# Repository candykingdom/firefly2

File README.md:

# Firefly2

Wireless LED control for Burning Man art installations, bikes, and wearables. Devices driving WS2812 strips self-organize over 915 MHz RFM69 radios into a flood mesh with exactly one master, share a network clock via heartbeats, and render effects as pure functions of network time — so every device animates in sync without streaming frames.

New to the project? Start with [GETTING_STARTED.md](GETTING_STARTED.md). Working in the code (human or agent)? The mental model lives in [docs/index.md](docs/index.md) and the shared Claude Code/Codex ground rules in [CLAUDE.md](CLAUDE.md).

## Web simulator (test without hardware)

```bash
python3 -m http.server 8642 -d sim
# open http://localhost:8642/
```

A zero-dependency browser simulator of the whole system: every effect and palette on the real device catalog, synced to a scrubbable network clock, with master-mode autoplay and control overrides. Byte-exact against the firmware (enforced by tests: `npm test`). See [docs/simulator.md](docs/simulator.md).

## Building firmware

Firmware builds with [PlatformIO](https://platformio.org/) (`pip install platformio`). One env per device target:

```bash
pio run -e node                  # SAMD21 rfboard node (node-arm64 on Apple silicon)
pio run -e fancy-node            # STM32G030 node
pio run -e controller            # STM32G070 handheld controller
pio run -e dmx                   # ESP32 DMX bridge
pio run -e fancy-node -t upload  # flash via ST-Link
pio device monitor               # 115200 baud
```

Note: `[env:node]`'s bossac `platform_packages` entry is OS-specific — uncomment the right line in [platformio.ini](platformio.ini) for your OS. Full env/pin/flag details: [docs/build-and-test.md](docs/build-and-test.md).

### Programming over USB

The `fancy-node` device can be programmed either using an STLink, or via USB port. To program via USB, you must first install stm32loader using pip (`pip install stm32loader`). You may also need to pass the port (typically `/dev/ttyUSB0`), e.g. `pio run -e fancy-node-usb -t upload --upload-port /dev/ttyUSB0`.

### Saving device description in flash

Both `node` and `fancy-node` support reading the [`DeviceDescription`](lib/device/DeviceDescription.hpp) from flash. The modes are defined by the `DeviceMode` enum within [`DeviceDescription.hpp`](lib/device/DeviceDescription.hpp). They work as follows:

- `CURRENT_FROM_HEADER`: use the `current` device defined in [`Devices.hpp`](lib/device/Devices.hpp)
- `READ_FROM_FLASH`: read the device saved in flash, if present. If not present (determined by the validity of `check_value`), fall back to `current`.
- `WRITE_TO_FLASH`: write `current` to flash, and then use it. This will only write the device to flash if it is different, to avoid causing flash wear.

## Tests & linting

The platform-independent core (`lib/`, `src/generic/`) builds on the host against fakes, with ASan + UBSan on (and fatal). Requires cmake and a GCC/Clang toolchain (on Windows, use WSL or similar):

```bash
mkdir -p build && cd build
cmake .. -DBUILD_SIMULATOR=false   # true builds the SDL desktop simulator too
make && make test
./smalltests --gtest_filter=RadioStateMachineTest*
```

```bash
./lint.sh check     # clang-format, Google style — CI enforces this
./lint.sh format    # format in place
./ci.sh             # exactly what CI runs: cmake + smalltests + largetests
node --test "sim/test/cases/*.test.mjs"   # simulator suite, incl. firmware byte-exactness
npm run test:e2e    # served UI/API/canvas journeys in Chromium and Firefox
```

CI (GitHub Actions): host tests, lint, `node`/`fancy-node`/`controller` firmware
builds, the simulator suite, and CodeQL C/C++ security scanning.

## Repo layout

| Path | Contents |
|---|---|
| `lib/`, `src/generic/` | Platform-independent core: radio protocol, mesh, effects, LED management |
| `src/arduino/` | Hardware backends (FastLED, RadioHead RFM69) |
| `src/devices/` | One `main` per device target (node, fancy-node, controller, dmx) |
| `test/` | Host GoogleTest suites + `FakeNetwork` multi-node mesh simulation |
| `sim/` | Browser simulator (production C++ renderer via committed Wasm, usable without hardware) |
| `docs/` | Architecture and per-subsystem notes — start at [docs/index.md](docs/index.md) |
| `hardware/`, `boards/`, `bootloader/` | PCB designs, PlatformIO board definitions, bootloaders |
| `specs/` | Spec-kit feature specs (spec → plan → tasks workflow, see CLAUDE.md) |

## For agents & contributors

- [CLAUDE.md](CLAUDE.md) — the canonical guidance for Claude Code and Codex, including build commands, architecture, and the **invariants you must not break**. Codex reaches the same file through `AGENTS.md`; shared skills remain canonical under `.claude/skills/` and are exposed to Codex through `.agents/skills/`.
- [docs/](docs/index.md) — per-subsystem research notes (radio/network, LED/effects, devices, build/test, hardware). Update them when you change documented behavior.
- Substantial features go through the spec-kit workflow (`speckit-specify` → `plan` →
  `tasks` → `implement`; use `/` in Claude Code or `$` in Codex); specs live in `specs/`.

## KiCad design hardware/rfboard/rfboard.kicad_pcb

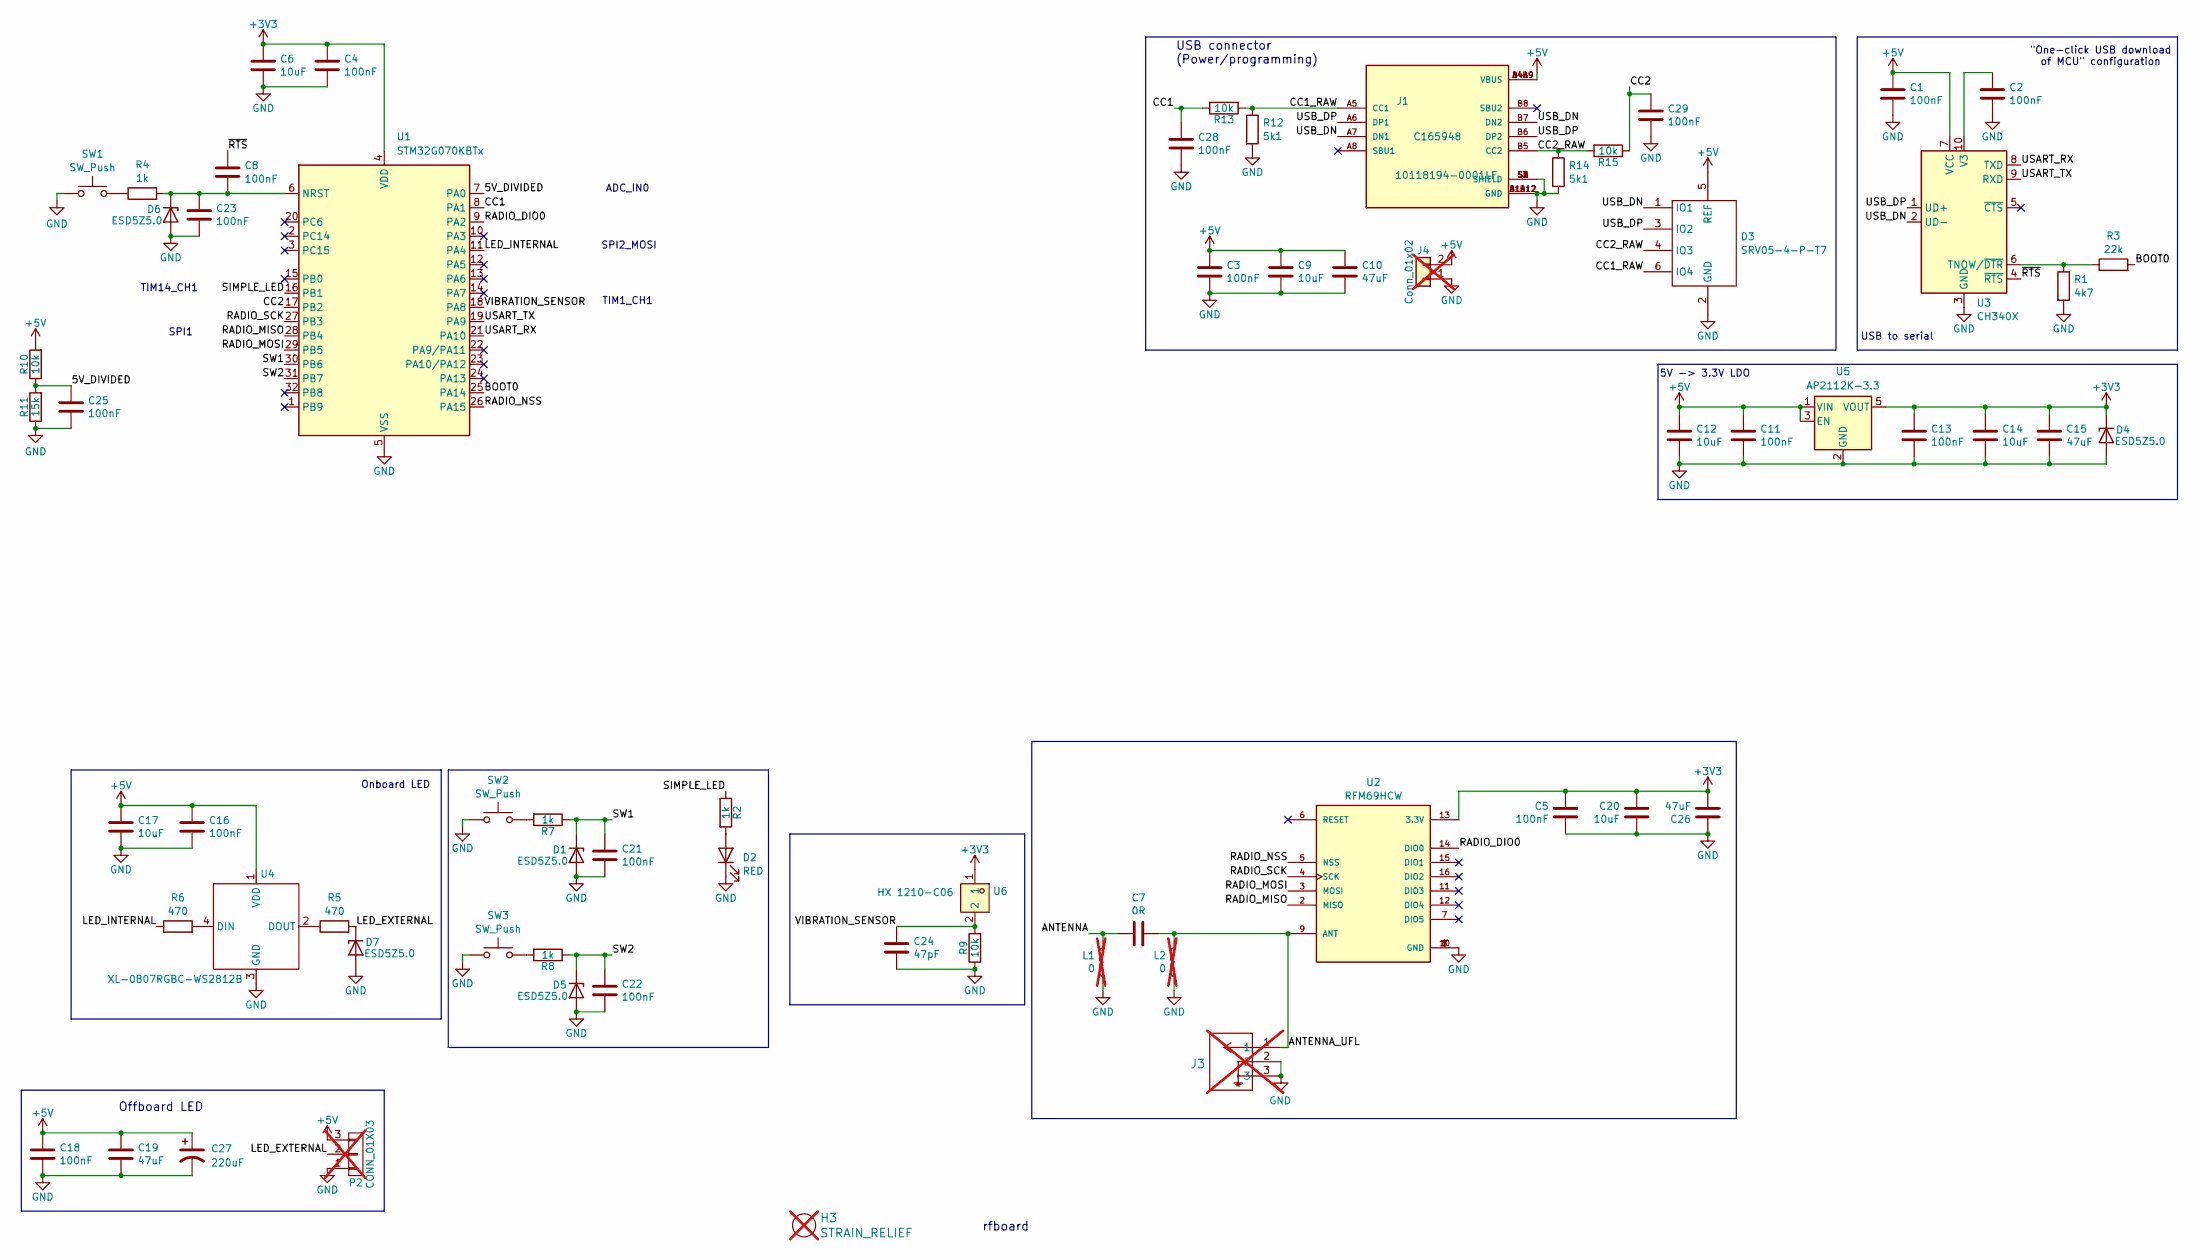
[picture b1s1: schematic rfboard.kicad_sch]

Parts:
C1, C2, C3, C4, C5, C8, C11, C13, C16, C18, C21, C22, C23, C25, C28, C29: 100nF; C_0402_1005Metric; LCSC C307331
C6, C9, C12, C14, C17, C20: 10uF; C_0603_1608Metric; LCSC C96446
C7: 0R; C_0402_1005Metric_Pad0.74x0.62mm_HandSolder; LCSC C17168
C10, C15, C19, C26: 47uF; C_1206_3216Metric; LCSC C426659
C24: 47pF; C_0402_1005Metric; LCSC C1567
C27: 220uF; CP_Elec_6.3x5.8; Voltage 16V; LCSC C25170689
D1, D4, D5, D6, D7: ESD5Z5.0; D_SOD-523; LCSC C5199848
D2: RED; LED_0603_1608Metric; LCSC C2286
D3: SRV05-4-P-T7; SOT-23-6; LCSC C85364
H3: STRAIN_RELIEF; 3_pin_2.54mm_pitch_strain_relief; not fitted
J1: 10118194-0001LF; HRO_TYPE-C-31-M-12; PARTREV A; LCSC C165948
J3: 2337019-1; CONN_2337019-1; MPN 2337019-1; not fitted
J4: Conn_01x02; PinHeader_1x02_P2.54mm_Vertical_NoPlastic; not fitted
L1, L2: 0; L_0402_1005Metric_Pad0.77x0.64mm_HandSolder; not fitted
P2: CONN_01X03; PinHeader_1x03_P2.54mm_Vertical; not fitted
R1: 4k7; R_0402_1005Metric; LCSC C25900
R2, R4, R7, R8: 1k; R_0402_1005Metric; LCSC C11702
R3: 22k; R_0402_1005Metric; LCSC C25768
R5, R6: 470; R_0402_1005Metric; LCSC C25117
R9, R10, R13, R15: 10k; R_0402_1005Metric; LCSC C25744
R11: 15k; R_0402_1005Metric; LCSC C25756
R12, R14: 5k1; R_0402_1005Metric; LCSC C25905
SW1, SW2, SW3: SW_Push; SW_TACTILE_5.1MM_TS-1187A-C-D-B; LCSC C318884
U1: STM32G070KBTx; LQFP-32_7x7mm_P0.8mm; LCSC C529339
U2: RFM69HCW; RFM69HCW-minimalpads
U3: CH340X; MSOP-10_3x3mm_P0.5mm; LCSC C3035748
U4: XL-0807RGBC-WS2812B; LED-SMD_4P-L2.0-W1.8_CY-0807; LCSC C3646929
U5: AP2112K-3.3; SOT-23-5; LCSC C51118
U6: HX 1210-C06; SMD-2P_L2.9-W2.4_C9900033648; LCSC Part C42371120

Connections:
+3V3: C4.1, C5.1, C6.1, C13.1, C14.1, C15.1, C20.1, C26.2, D4.1 (K), U1.4 (VDD), U2.13 (3.3V), U5.5 (VOUT), U6.1
+5V: C1.1, C3.1, C9.1, C10.1, C11.1, C12.1, C16.1, C17.1, C18.1, C19.1, C27.1, D3.5 (REF), J1.A4B9 (VBUS), J1.B4A9 (VBUS), J4.2, P2.3, R10.2, U3.7 (VCC), U4.1 (VDD), U5.1 (VIN), U5.3 (EN)
/5V_DIVIDED: C25.1, R10.1, R11.2, U1.7 (PA0)
/ANTENNA: C7.1, L1.1
/ANTENNA_UFL: C7.2, J3.1, L2.1, U2.9 (ANT)
/BOOT0: R3.2, U1.25 (PA14)
/CC1: C28.1, R13.2, U1.8 (PA1)
/CC1_RAW: D3.6 (IO4), J1.A5 (CC1), R12.1, R13.1
/CC2: C29.1, R15.1, U1.17 (PB2)
/CC2_RAW: D3.4 (IO3), J1.B5 (CC2), R14.1, R15.2
/LED_EXTERNAL: D7.1 (K), P2.2, R5.2
/LED_INTERNAL: R6.1, U1.11 (PA4)
/RADIO_DIO0: U1.9 (PA2), U2.14 (DIO0)
/RADIO_MISO: U1.28 (PB4), U2.2 (MISO)
/RADIO_MOSI: U1.29 (PB5), U2.3 (MOSI)
/RADIO_NSS: U1.26 (PA15), U2.5 (NSS)
/RADIO_SCK: U1.27 (PB3), U2.4 (SCK)
/SIMPLE_LED: R2.1, U1.16 (PB1)
/SW1: C21.1, D1.1 (K), R7.1, U1.30 (PB6)
/SW2: C22.1, D5.1 (K), R8.1, U1.31 (PB7)
/USART_RX: U1.21 (PA10), U3.8 (TXD)
/USART_TX: U1.19 (PA9), U3.9 (RXD)
/USB_DN: D3.1 (IO1), J1.A7 (DN1), J1.B7 (DN2), U3.2 (UD-)
/USB_DP: D3.3 (IO2), J1.A6 (DP1), J1.B6 (DP2), U3.1 (UD+)
/VIBRATION_SENSOR: C24.1, R9.2, U1.18 (PA8), U6.2
/~RTS: C8.1, U3.4 (~RTS)
GND: C1.2, C2.2, C3.2, C4.2, C5.2, C6.2, C9.2, C10.2, C11.2, C12.2, C13.2, C14.2, C15.2, C16.2, C17.2, C18.2, C19.2, C20.2, C21.2, C22.2, C23.2, C24.2, C25.2, C26.1, C27.2, C28.2, C29.2, D1.2 (A), D2.1 (K), D3.2 (GND), D4.2 (A), D5.2 (A), D6.2 (A), D7.2 (A), J1.A1B12 (GND), J1.B1A12 (GND), J1.S1 (SHIELD), J1.S2 (SHIELD), J1.S3 (SHIELD), J1.S4 (SHIELD), J3.2, J3.3, J4.1, L1.2, L2.2, P2.1, R1.2, R9.1, R11.1, R12.2, R14.2, SW1.1, SW2.1, SW3.1, U1.5 (VSS), U2.1 (GND), U2.8 (GND), U2.10 (GND), U3.3 (GND), U4.3 (GND), U5.2 (GND)
unnamed: D2.2 (A), R2.2
unnamed: C8.2, C23.1, D6.1 (K), R4.2, U1.6 (NRST)
unnamed: R4.1, SW1.2
unnamed: R7.2, SW2.2
unnamed: R8.2, SW3.2
unnamed: R1.1, R3.1, U3.6 (TNOW/~DTR)
unnamed: C2.1, U3.10 (V3)
unnamed: R6.2, U4.4 (DIN)
unnamed: R5.1, U4.2 (DOUT)

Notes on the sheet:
5V -> 3.3V LDO
USB connector (Power/programming)
rfboard
TIM14_CH1
Offboard LED
SPI2_MOSI
USB to serial
"One-click USB download of MCU" configuration
SPI1
ADC_IN0
TIM1_CH1
Onboard LED

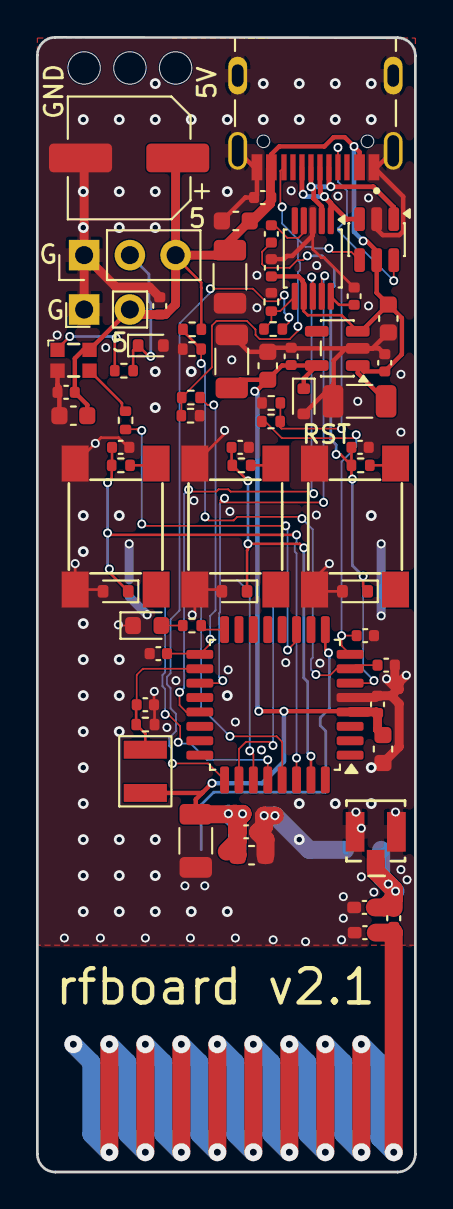
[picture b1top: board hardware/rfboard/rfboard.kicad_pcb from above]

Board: 4 copper layers, 21.0 x 63.0 mm, 67 parts (1 on the bottom side), 36 nets.

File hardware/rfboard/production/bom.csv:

Designator,Footprint,Quantity,Value,LCSC Part #
"C1, C11, C13, C16, C18, C2, C21, C22, C23, C25, C28, C29, C3, C4, C5, C8",0402,16,100nF,C307331
"C10, C15, C19, C26",1206,4,47uF,C96123
"C12, C14, C17, C20, C6, C9",0603,6,10uF,C96446
C24,0402,1,47pF,C1567
C27,CP_Elec_6.3x5.8,1,220uF,C25170689
C7,0402,1,0R,C17168
"D1, D4, D5, D6, D7",D_SOD-523,5,ESD5Z5.0,C5199848
D2,0603,1,RED,C2286
D3,SOT-23-6,1,SRV05-4-P-T7,C85364
J1,HRO_TYPE-C-31-M-12,1,10118194-0001LF,C165948
R1,0402,1,4k7,C25900
"R10, R13, R15, R9",0402,4,10k,C25744
R11,0402,1,15k,C25756
"R12, R14",0402,2,5k1,C25905
"R2, R4, R7, R8",0402,4,1k,C11702
R3,0402,1,22k,C25768
"R5, R6",0402,2,470,C25117
"SW1, SW2, SW3",SW_TACTILE_5.1MM_TS-1187A-C-D-B,3,SW_Push,C318884
U1,LQFP-32_7x7mm_P0.8mm,1,STM32G070KBTx,C529339
U2,RFM69HCW-minimalpads,1,RFM69HCW,
U3,MSOP-10_3x3mm_P0.5mm,1,CH340X,C3035748
U4,LED-SMD_4P-L2.0-W1.8_CY-0807,1,XL-0807RGBC-WS2812B,C3646929
U5,SOT-23-5,1,AP2112K-3.3,C51118
U6,SMD-2P_L2.9-W2.4_C9900033648,1,HX 1210-C06,C42371120

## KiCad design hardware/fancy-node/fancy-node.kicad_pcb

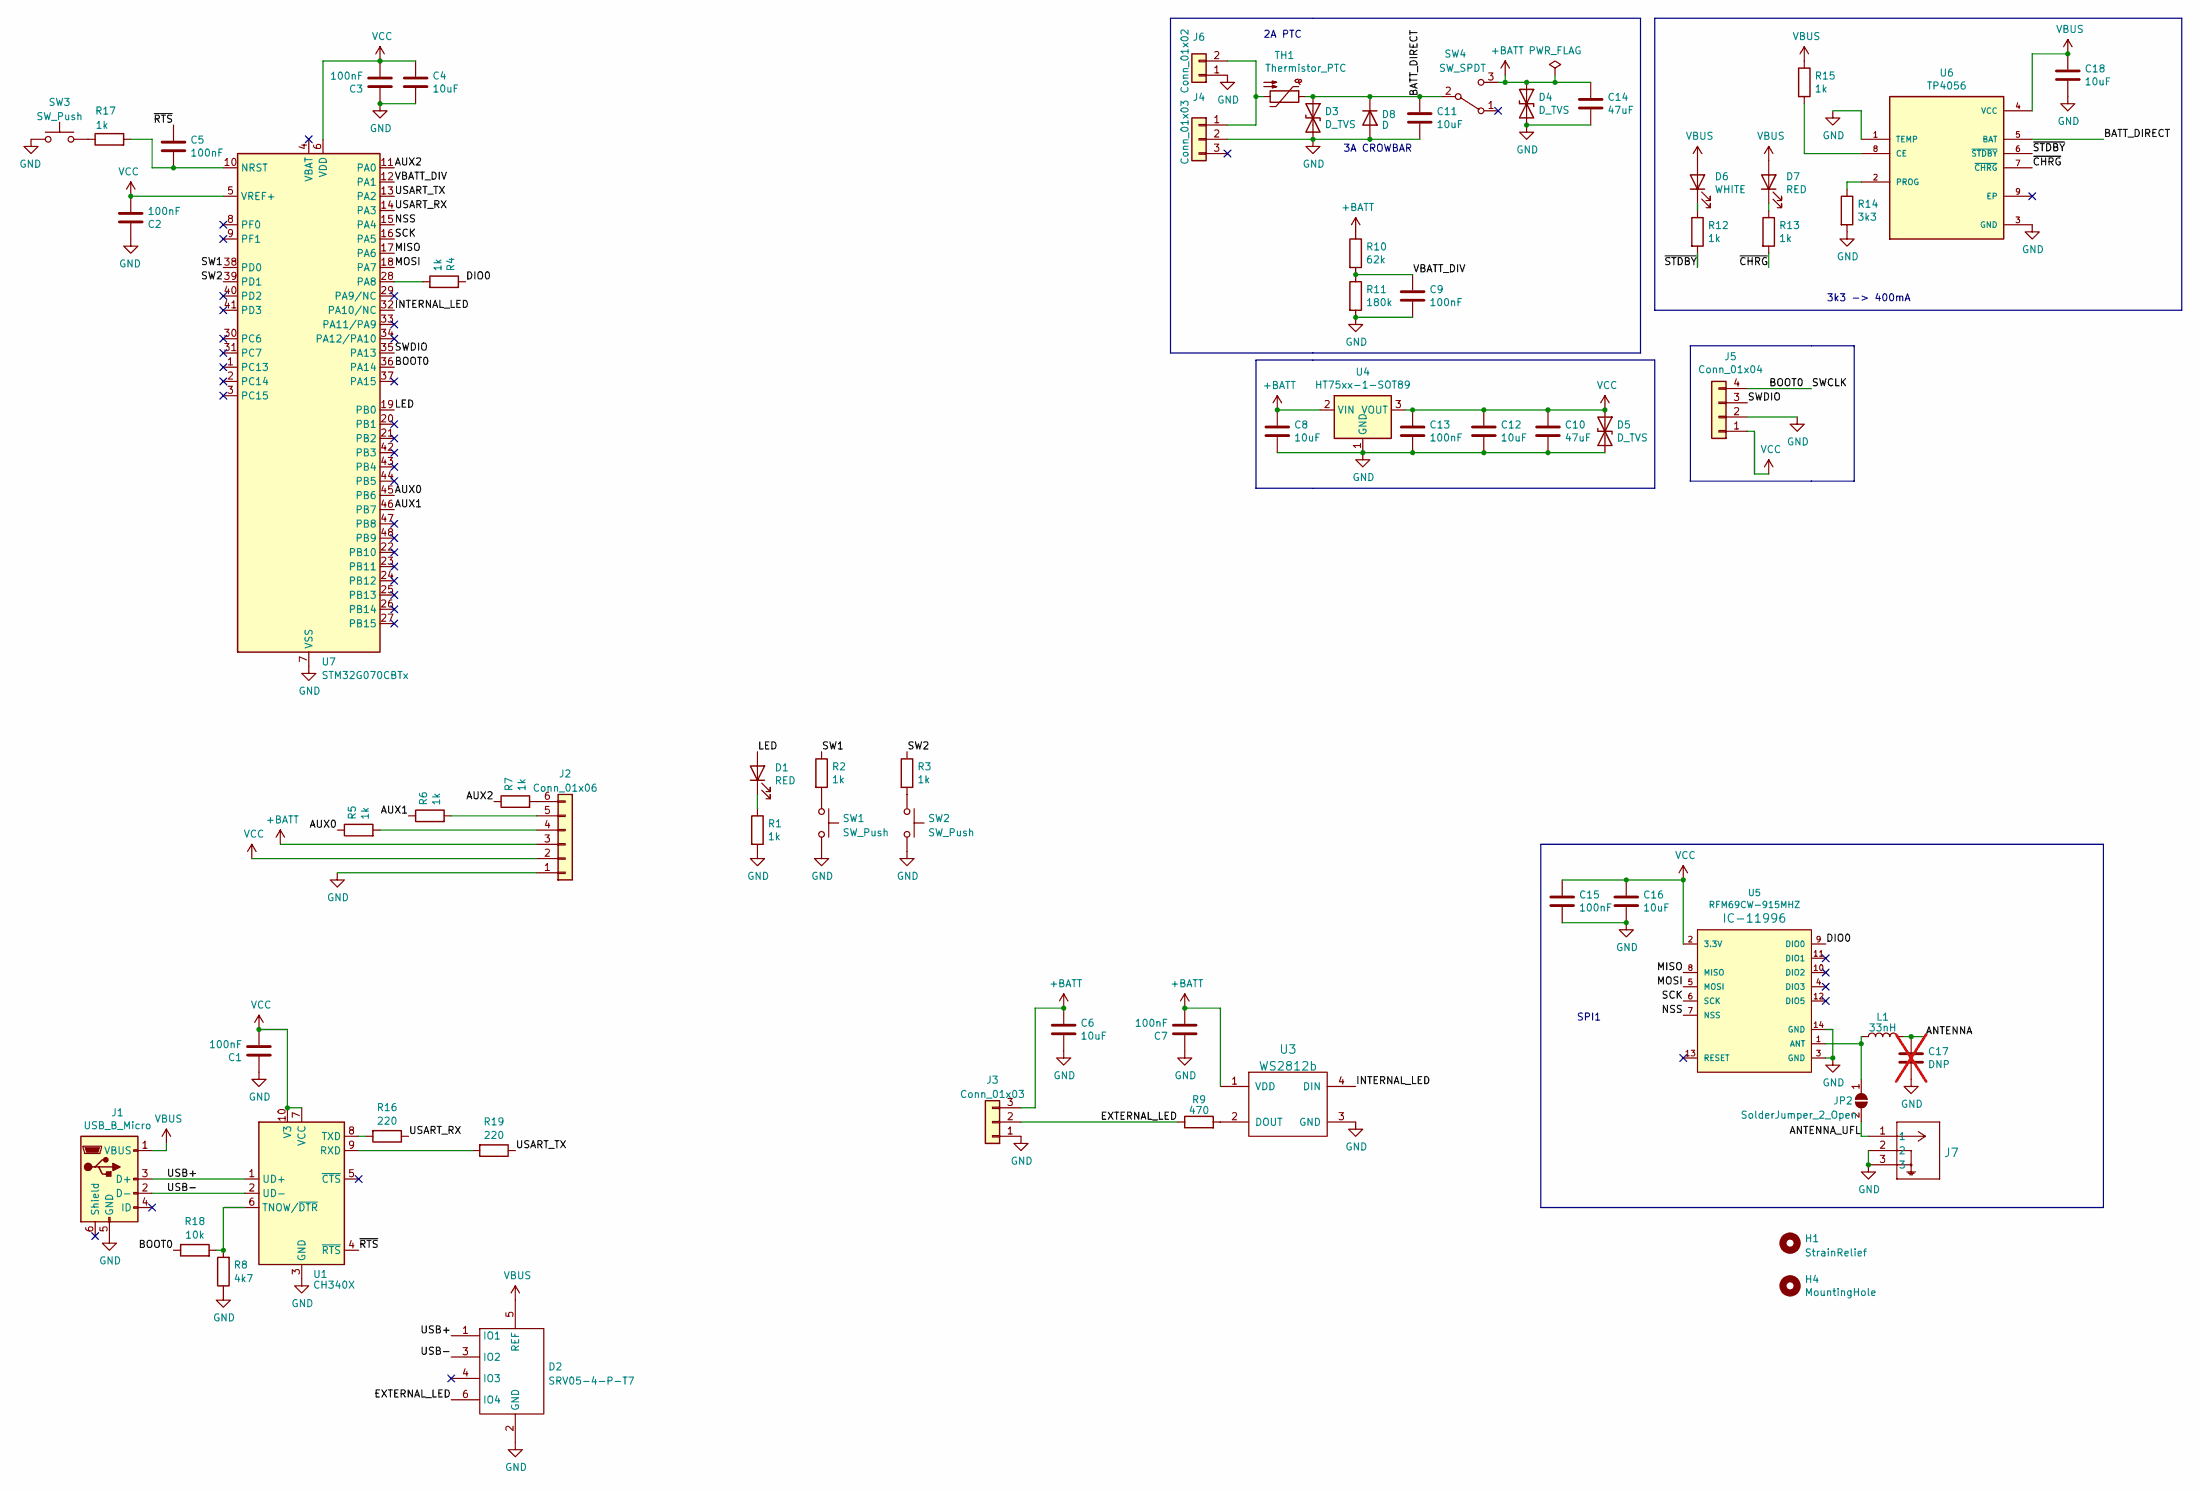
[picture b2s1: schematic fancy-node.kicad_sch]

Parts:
C1, C2, C3, C5, C7, C9, C13, C15: 100nF; C_0402_1005Metric_Pad0.74x0.62mm_HandSolder; LCSC C307331
C4, C6, C8, C11, C12, C16, C18: 10uF; C_0603_1608Metric; LCSC C96446
C10, C14: 47uF; C_1206_3216Metric; LCSC C96123
C17: DNP; C_0402_1005Metric_Pad0.74x0.62mm_HandSolder; not fitted
D1, D7: RED; LED_0603_1608Metric; LCSC C2286
D2: SRV05-4-P-T7; SOT-23-6; LCSC C85364
D3, D4, D5: D_TVS; D_SMB; LCSC C78395
D6: WHITE; LED_0603_1608Metric; LCSC C2290
D8: D; D_SMA; LCSC C8678
H1: StrainRelief; 3_pin_2.54mm_pitch_strain_relief
H4: MountingHole; MountingHole_3.2mm_M3
J1: USB_B_Micro; FRAMATOME_10118194-0001LF_fixed_bridges; LCSC C132563
J2: Conn_01x06; PinHeader_1x06_P2.54mm_Vertical
J3: Conn_01x03; PinHeader_1x03_P2.54mm_Horizontal
J4: Conn_01x03; MiniPV_78208-X03XXX_1x03_P2.54mm_Polarized_Horizontal
J5: Conn_01x04; PinHeader_1x04_P2.54mm_Vertical
J6: Conn_01x02; JST_Micro_1x02_P1.25mm_Horizontal
J7: 2337019-1; CONN_2337019-1; MPN 2337019-1
JP2: SolderJumper_2_Open; SolderJumper-2_P1.3mm_Open_TrianglePad1.0x1.5mm
L1: 33nH; L_0402_1005Metric; LCSC C113114
R1, R2, R3, R4, R5, R6, R7, R12, R13, R15, R17: 1k; R_0402_1005Metric; LCSC C11702
R8: 4k7; R_0402_1005Metric; LCSC C25900
R9: 470; R_0603_1608Metric; LCSC C23179
R10: 62k; R_0603_1608Metric; LCSC C23221
R11: 180k; R_0603_1608Metric; LCSC C22827
R14: 3k3; R_0603_1608Metric; LCSC C22978
R16, R19: 220; R_0402_1005Metric; LCSC C25091
R18: 10k; R_0402_1005Metric; LCSC C25744
SW1, SW2, SW3: SW_Push; SW_TACTILE_3mmx3.5mm_TS-1071SA-A4B3-D4; LCSC C498310
SW4: SW_SPDT; SW_SLIDE_SPDT_K3-1204D-L; LCSC C2909229
TH1: Thermistor_PTC; Fuse_1812_4532Metric_Pad1.30x3.40mm_HandSolder; LCSC C89650
U1: CH340X; MSOP-10_3x3mm_P0.5mm; LCSC C3035748
U3: WS2812b; LED_XINGLIGHT_WS2812B_PLCC4_5.0x5.0mm_P3.2mm; LCSC C2843785
U4: HT75xx-1-SOT89; SOT-89-3; LCSC C14289
U5: RFM69CW-915MHZ; RFM69CW-XXXS2
U6: TP4056; SOP-8_3.9x4.9mm_P1.27mm_Thermal; LCSC C382139
U7: STM32G070CBTx; LQFP-48_7x7mm_P0.5mm; LCSC C529338

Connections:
+BATT: C6.2, C7.2, C8.2, C14.2, D4.1 (A1), J2.3, J3.3, R10.1, SW4.3 (C), U3.1 (VDD), U4.2 (VIN)
/ANTENNA: C17.1, L1.2
/ANTENNA_UFL: J7.1, JP2.2 (B)
/AUX0: R5.1, U7.45 (PB6)
/AUX1: R6.1, U7.46 (PB7)
/AUX2: R7.1, U7.11 (PA0)
/BATT_DIRECT: C11.2, D3.1 (A1), D8.1 (K), SW4.2 (B), TH1.1, U6.5 (BAT)
/BOOT0: J5.4, R18.1, U7.36 (PA14)
/DIO0: R4.1, U5.9 (DIO0)
/EXTERNAL_LED: D2.6 (IO4), J3.2, R9.1
/INTERNAL_LED: U3.4 (DIN), U7.32 (PA10/NC)
/LED: D1.2 (A), U7.19 (PB0)
/MISO: U5.8 (MISO), U7.17 (PA6)
/MOSI: U5.5 (MOSI), U7.18 (PA7)
/NSS: U5.7 (NSS), U7.15 (PA4)
/SCK: U5.6 (SCK), U7.16 (PA5)
/SW1: R2.1, U7.38 (PD0)
/SW2: R3.1, U7.39 (PD1)
/SWDIO: J5.3, U7.35 (PA13)
/USART_RX: R16.1, U7.14 (PA3)
/USART_TX: R19.1, U7.13 (PA2)
/USB+: D2.1 (IO1), J1.3 (D+), U1.1 (UD+)
/USB-: D2.3 (IO2), J1.2 (D-), U1.2 (UD-)
/VBATT_DIV: C9.1, R10.2, R11.1, U7.12 (PA1)
/~CHRG: R13.2, U6.7 (~CHRG)
/~RTS: C5.1, U1.4 (~RTS)
/~STDBY: R12.2, U6.6 (~STDBY)
GND: C1.1, C2.1, C3.1, C4.2, C6.1, C7.1, C8.1, C9.2, C10.1, C11.1, C12.1, C13.2, C14.1, C15.2, C16.1, C17.2, C18.1, D2.2 (GND), D3.2 (A2), D4.2 (A2), D5.2 (A2), D8.2 (A), J1.5 (GND), J2.1, J3.1, J4.2, J5.2, J6.1, J7.2, J7.3, R1.2, R8.1, R11.2, R14.2, SW1.2, SW2.2, SW3.2, U1.3 (GND), U3.3 (GND), U4.1 (GND), U5.3 (GND), U5.14 (GND), U6.1 (TEMP), U6.3 (GND), U7.7 (VSS)
unnamed: D1.1 (K), R1.1
unnamed: D6.1 (K), R12.1
unnamed: D7.1 (K), R13.1
unnamed: J2.4, R5.2
unnamed: J2.5, R6.2
unnamed: J2.6, R7.2
unnamed: J4.1, J6.2, TH1.2
unnamed: JP2.1 (A), L1.1, U5.1 (ANT)
unnamed: R2.2, SW1.1
unnamed: R3.2, SW2.1
unnamed: R17.1, SW3.1
unnamed: R19.2, U1.9 (RXD)
unnamed: R8.2, R18.2, U1.6 (TNOW/~DTR)
unnamed: R16.2, U1.8 (TXD)
unnamed: R9.2, U3.2 (DOUT)
unnamed: R15.2, U6.8 (CE)
unnamed: R14.1, U6.2 (PROG)
unnamed: C5.2, R17.2, U7.10 (NRST)
unnamed: R4.2, U7.28 (PA8)
VBUS: C18.2, D2.5 (REF), D6.2 (A), D7.2 (A), J1.1 (VBUS), R15.1, U6.4 (VCC)
VCC: C1.2, C2.2, C3.2, C4.1, C10.2, C12.2, C13.1, C15.1, C16.2, D5.1 (A1), J2.2, J5.1, U1.7 (VCC), U1.10 (V3), U4.3 (VOUT), U5.2 (3.3V), U7.5 (VREF+), U7.6 (VDD)

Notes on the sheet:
3k3 -> 400mA
3A CROWBAR
SPI1
2A PTC

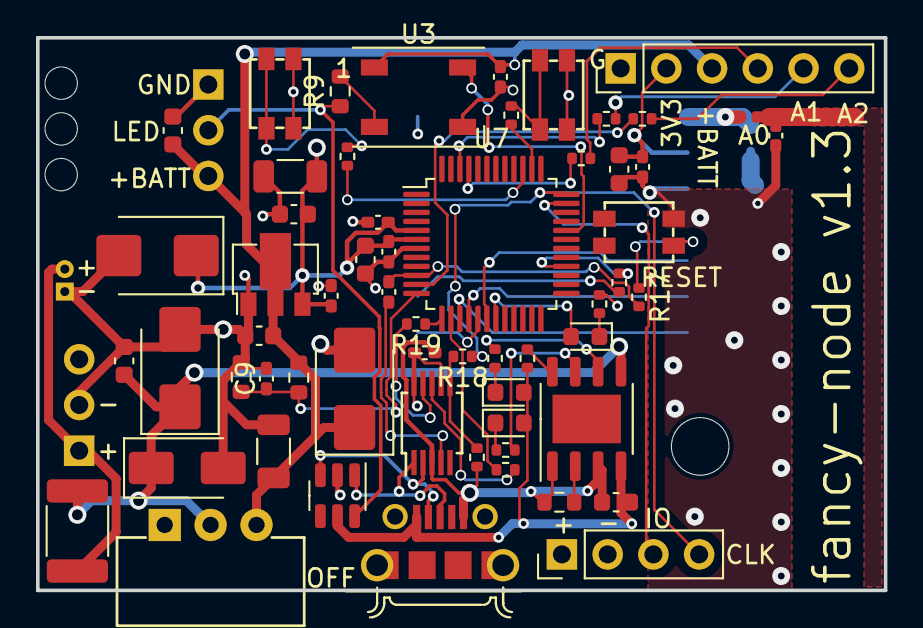
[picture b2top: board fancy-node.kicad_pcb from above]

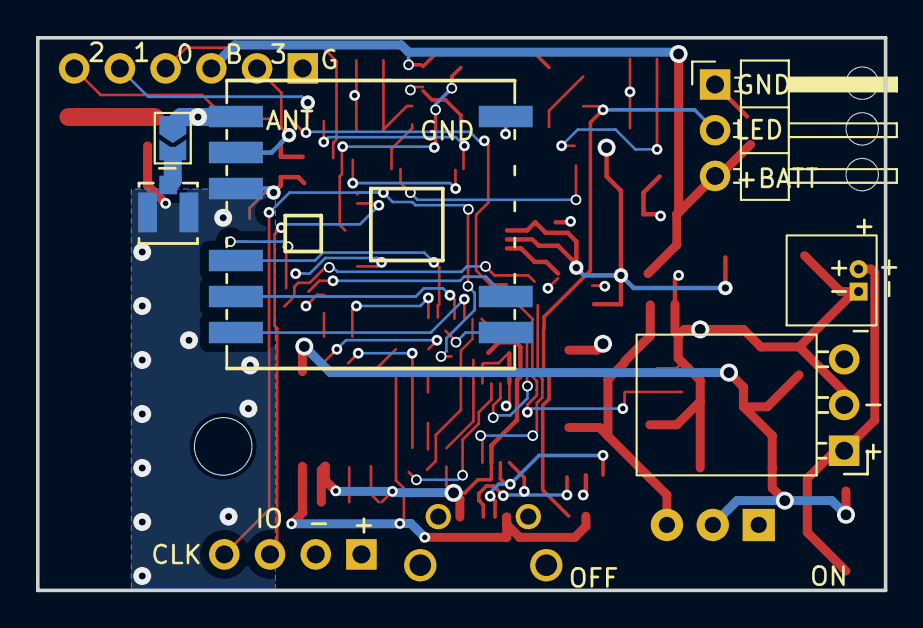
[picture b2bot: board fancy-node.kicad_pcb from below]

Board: 4 copper layers, 47.1 x 30.7 mm, 67 parts (6 on the bottom side), 49 nets.

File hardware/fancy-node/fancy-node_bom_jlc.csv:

"Comment","Designator","Footprint","LCSC Part #"
"100nF","C1,C2,C3,C5,C7,C9,C13,C15","C_0402_1005Metric_Pad0.74x0.62mm_HandSolder","C307331"
"10uF","C4,C6,C8,C11,C12,C16,C18","C_0603_1608Metric","C96446"
"47uF","C10,C14","C_1206_3216Metric","C96123"
"RED","D1,D7","LED_0603_1608Metric","C2286"
"SRV05-4-P-T7","D2","SOT-23-6","C85364"
"D_TVS","D3,D4,D5","D_SMB","C78395"
"WHITE","D6","LED_0603_1608Metric","C2290"
"D","D8","D_SMA","C8678"
"USB_B_Micro","J1","FRAMATOME_10118194-0001LF_fixed_bridges","C132563"
"33nH","L1","L_0402_1005Metric","C113114"
"1k","R1,R2,R3,R4,R5,R6,R7,R12,R13,R15,R17","R_0402_1005Metric","C11702"
"4k7","R8","R_0402_1005Metric","C25900"
"470","R9","R_0603_1608Metric","C23179"
"62k","R10","R_0603_1608Metric","C23221"
"180k","R11","R_0603_1608Metric","C22827"
"3k3","R14","R_0603_1608Metric","C22978"
"220","R16,R19","R_0402_1005Metric","C25091"
"10k","R18","R_0402_1005Metric","C25744"
"SW_Push","SW1,SW2,SW3","SW_TACTILE_3mmx3.5mm_TS-1071SA-A4B3-D4","C498310"
"SW_SPDT","SW4","SW_SLIDE_SPDT_K3-1204D-L","C2909229"
"Thermistor_PTC","TH1","Fuse_1812_4532Metric_Pad1.30x3.40mm_HandSolder","C89650"
"CH340X","U1","MSOP-10_3x3mm_P0.5mm","C3035748"
"WS2812b","U3","LED_XINGLIGHT_WS2812B_PLCC4_5.0x5.0mm_P3.2mm","C2843785"
"HT75xx-1-SOT89","U4","SOT-89-3","C14289"
"TP4056","U6","SOP-8_3.9x4.9mm_P1.27mm_Thermal","C382139"
"STM32G070CBTx","U7","LQFP-48_7x7mm_P0.5mm","C529338"
